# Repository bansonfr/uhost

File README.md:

# uhost
Minimalist Arduino host design v1.2

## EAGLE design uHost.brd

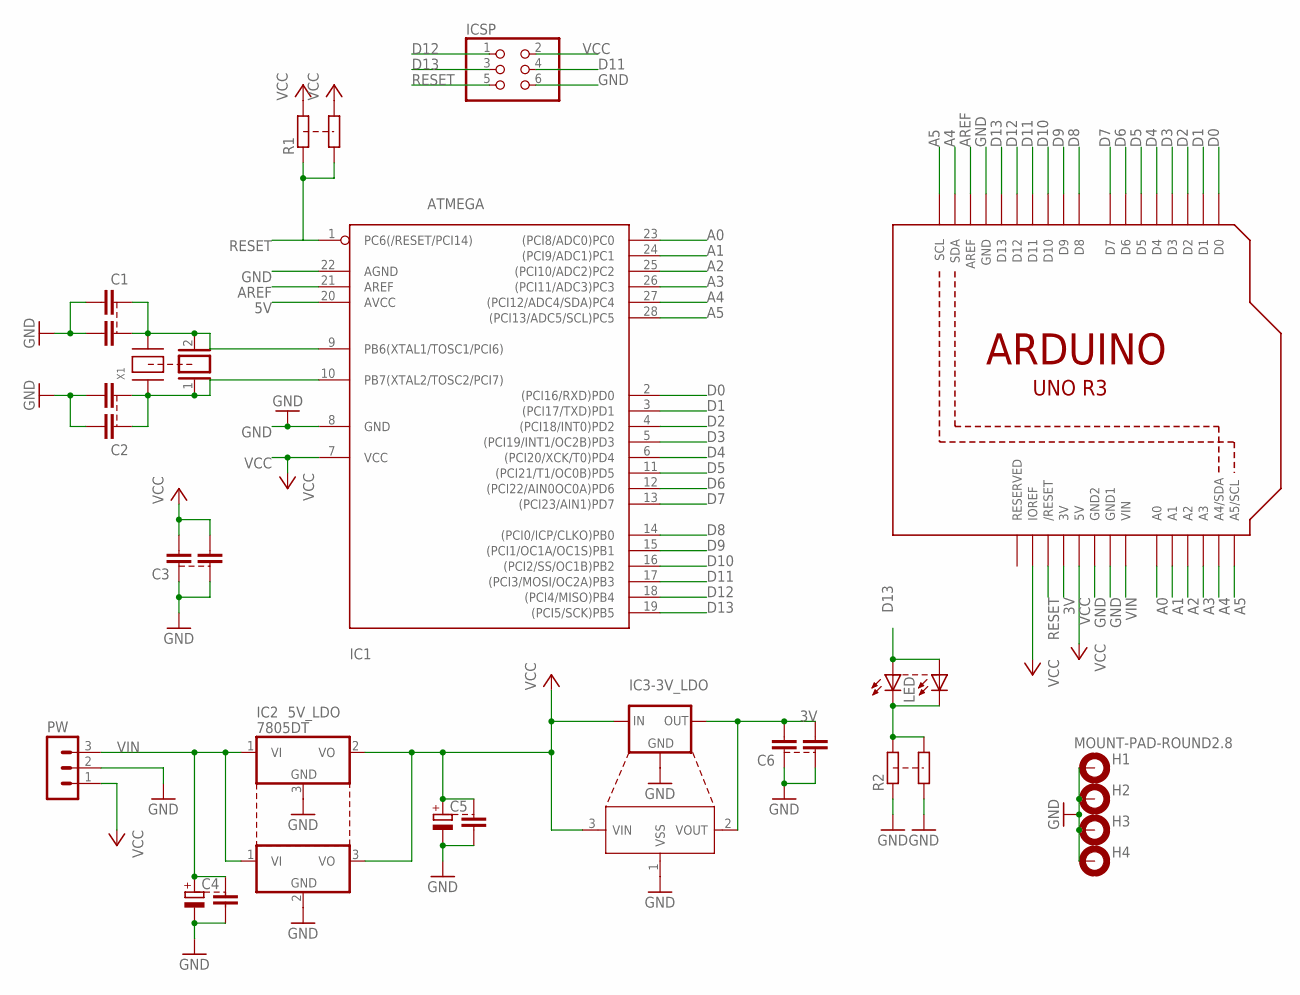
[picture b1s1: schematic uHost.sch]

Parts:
C1, C2, C23, C24, C25, C26: C-EUC1206; C1206
C3, C6, C21, C22: C-EU050-025X075; C050-025X075
C4, C5: CPOL-EUE2.5-6; E2,5-6
H1, H2, H3, H4: MOUNT-PAD-ROUND2.8; 2,8-PAD
IC1: ATMEGA; DIL28-3
IC2: 7805DT; TO252
IC3-3V_LDO: 78LXX
IC23: 5V_LDO; TO220H
ICSP: PINHD-2X3; 2X03
LED: LED3MM
LED1: LEDCHIPLED_1206; CHIPLED_1206
PW: MA03-1
Q2: XTAL/S; QS
R1, R2: R-EU_0207/7; 0207/7
R21, R22: R-EU_R1206; R1206
U1: ARDUINOR3-BPLACE
U2: XC6206-3.3-1300260P1; SOT23
X1: XTALNX5032; NX5032

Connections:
3V: C6.2, C26.2, IC3-3V_LDO.OUT, U1.3V, U2.2 (VOUT)
5V: IC1.20 (AVCC)
A0: IC1.23 ((PCI8/ADC0)PC0), U1.A0
A1: IC1.24 ((PCI9/ADC1)PC1), U1.A1
A2: IC1.25 ((PCI10/ADC2)PC2), U1.A2
A3: IC1.26 ((PCI11/ADC3)PC3), U1.A3
A4: IC1.27 ((PCI12/ADC4/SDA)PC4), U1.A4 (A4/SDA), U1.SDA
A5: IC1.28 ((PCI13/ADC5/SCL)PC5), U1.A5 (A5/SCL), U1.SCL
AREF: IC1.21 (AREF), U1.AREF
D0: IC1.2 ((PCI16/RXD)PD0), U1.D0
D1: IC1.3 ((PCI17/TXD)PD1), U1.D1
D2: IC1.4 ((PCI18/INT0)PD2), U1.D2
D3: IC1.5 ((PCI19/INT1/OC2B)PD3), U1.D3
D4: IC1.6 ((PCI20/XCK/T0)PD4), U1.D4
D5: IC1.11 ((PCI21/T1/OC0B)PD5), U1.D5
D6: IC1.12 ((PCI22/AIN0OC0A)PD6), U1.D6
D7: IC1.13 ((PCI23/AIN1)PD7), U1.D7
D8: IC1.14 ((PCI0/ICP/CLKO)PB0), U1.D8
D9: IC1.15 ((PCI1/OC1A/OC1S)PB1), U1.D9
D10: IC1.16 ((PCI2/SS/OC1B)PB2), U1.D10
D11: IC1.17 ((PCI3/MOSI/OC2A)PB3), ICSP.4, U1.D11
D12: IC1.18 ((PCI4/MISO)PB4), ICSP.1, U1.D12
D13: IC1.19 ((PCI5/SCK)PB5), ICSP.3, LED.A, LED1.A, U1.D13
GND: C1.2, C2.2, C3.1, C4.-, C5.-, C6.1, C21.2, C22.2, C23.1, C24.2, C25.2, C26.1, H1.B2,8, H2.B2,8, H3.B2,8, H4.B2,8, IC1.8 (GND), IC1.22 (AGND), IC2.3 (GND), IC3-3V_LDO.GND, IC23.2 (GND), ICSP.6, PW.2, R2.1, R22.1, U1.GND, U1.GND1, U1.GND2, U2.1 (VSS)
unnamed: LED.K (C), LED1.C, R2.2, R22.2
unnamed: C1.1, C21.1, IC1.9 (PB6(XTAL1/TOSC1/PCI6)), Q2.2, X1.P$2
unnamed: C2.1, C22.1, IC1.10 (PB7(XTAL2/TOSC2/PCI7)), Q2.1, X1.P$1
RESET: IC1.1 (PC6(/RESET/PCI14)), ICSP.5, R1.1, R21.1, U1.RESET (/RESET)
VCC: C3.2, C5.+, C23.2, C25.1, IC1.7 (VCC), IC2.2 (VO), IC3-3V_LDO.IN, IC23.3 (VO), ICSP.2, PW.1, R1.2, R21.2, U1.5V, U1.IOREF, U2.3 (VIN)
VIN: C4.+, C24.1, IC2.1 (VI), IC23.1 (VI), PW.3, U1.VIN

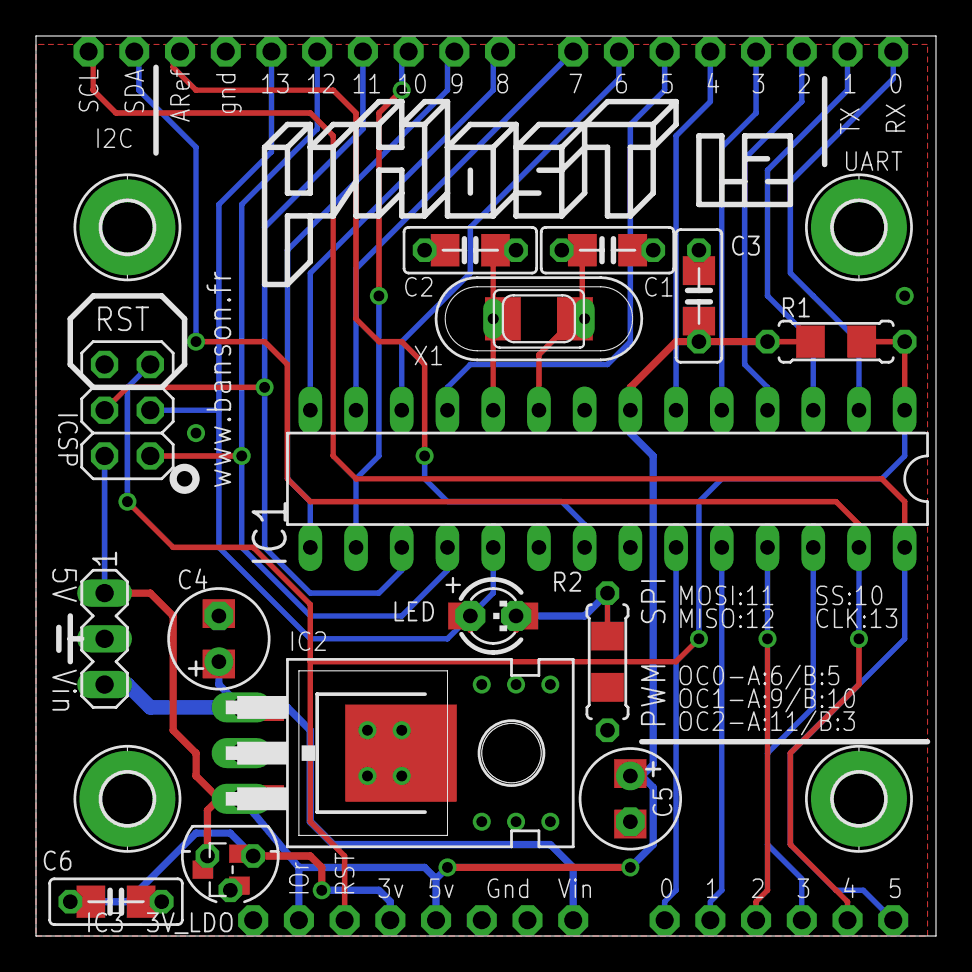
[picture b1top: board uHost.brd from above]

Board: 2 copper layers, 50.0 x 50.0 mm, 32 parts (0 on the bottom side), 29 nets.

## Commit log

2015-05-21 Initial Release v1.2
